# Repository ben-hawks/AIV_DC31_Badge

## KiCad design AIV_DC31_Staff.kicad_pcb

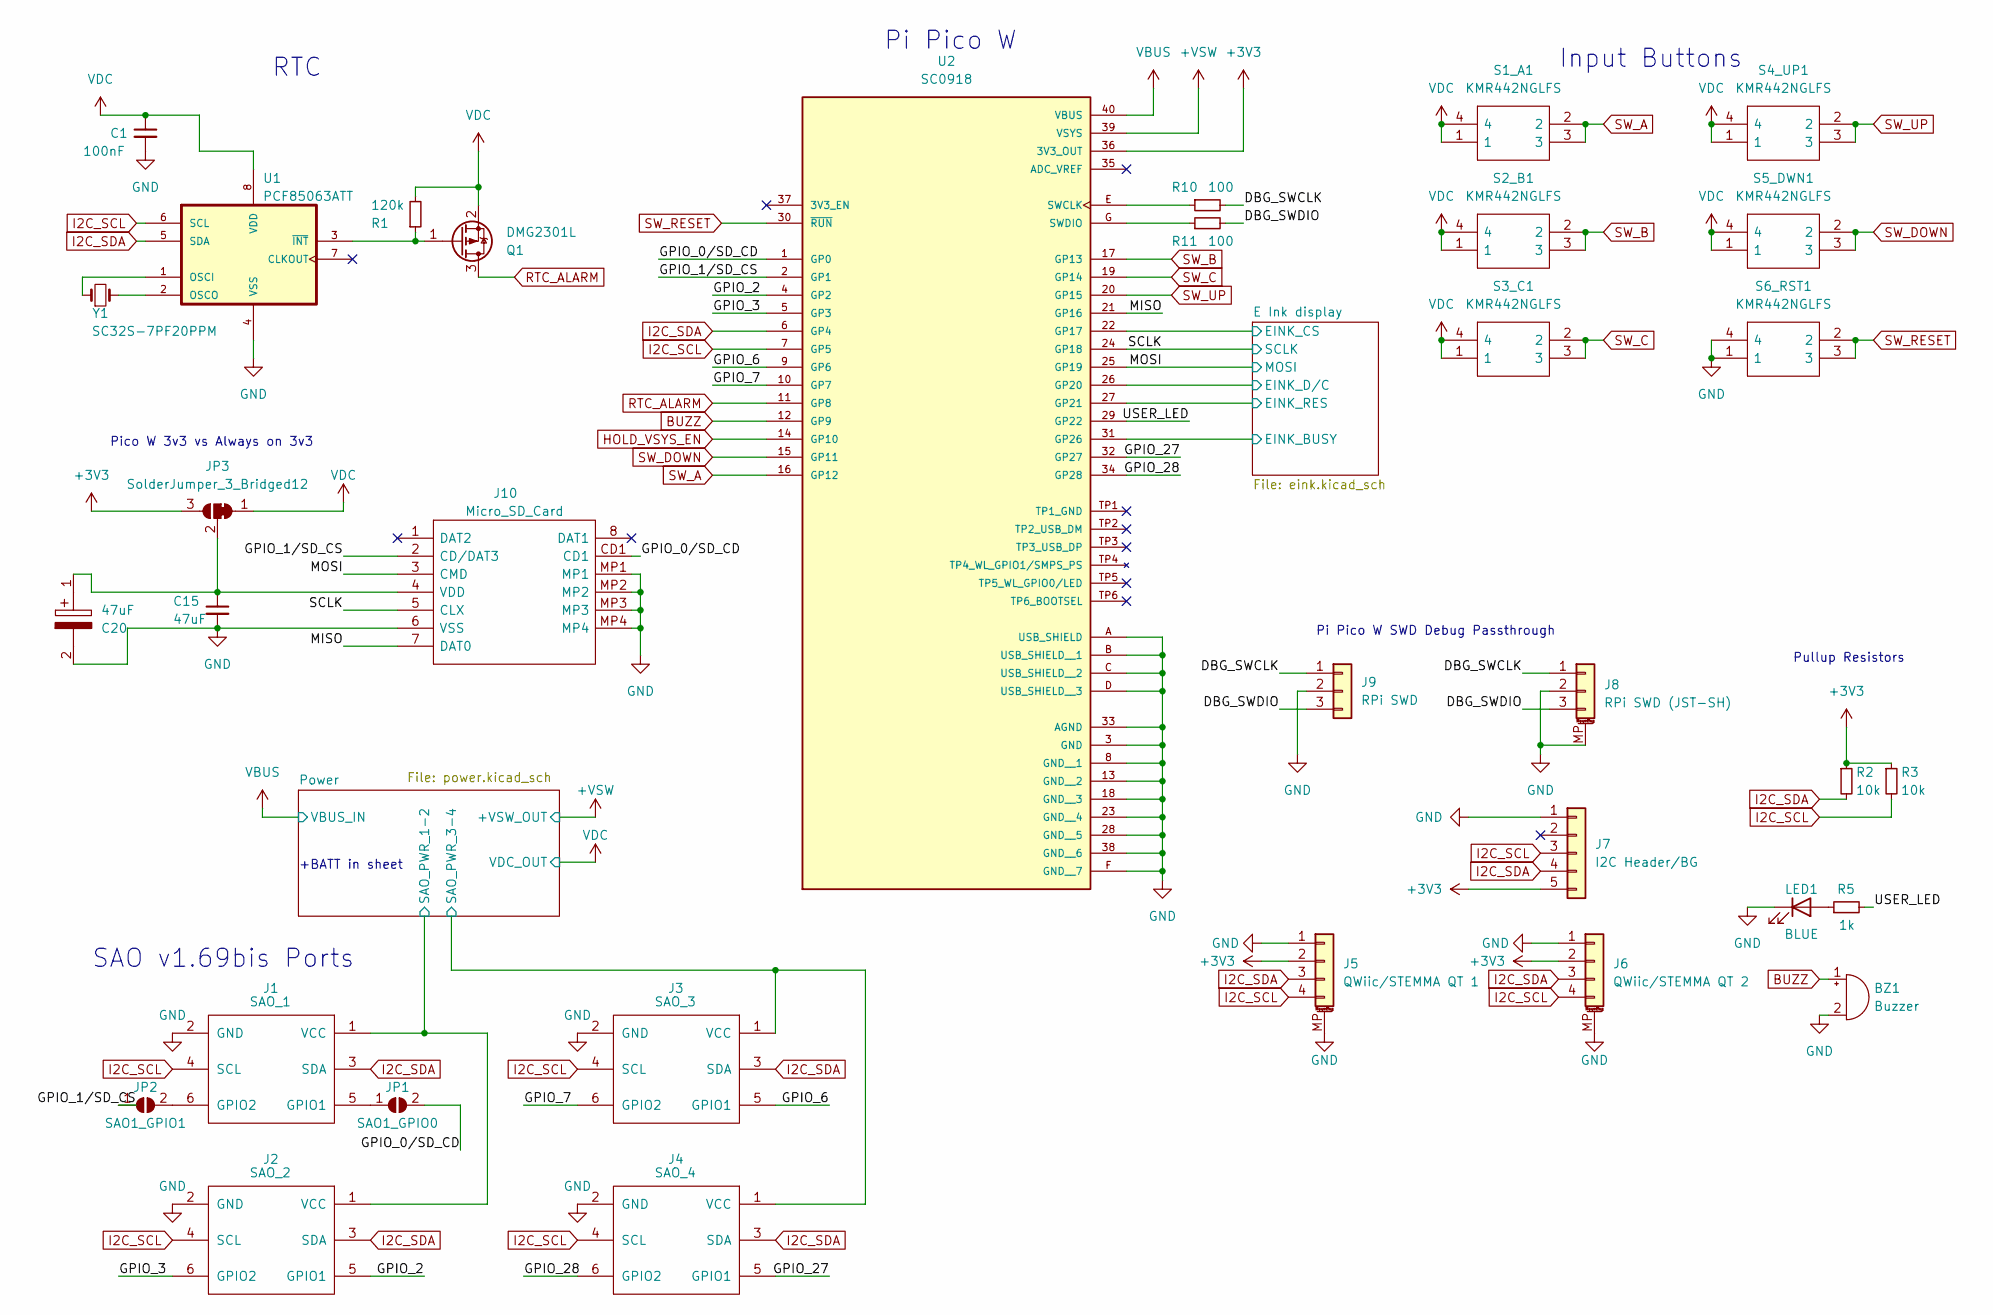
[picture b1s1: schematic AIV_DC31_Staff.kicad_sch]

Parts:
BZ1: Buzzer; Buzzer_CUI_CPT-9019S-SMT
C1: 100nF; C_0805_2012Metric_Pad1.18x1.45mm_HandSolder
C15: 47uF; C_0805_2012Metric_Pad1.18x1.45mm_HandSolder
C20: 47uF; CAPAE660X630N; Mouser Part Number 661-HHXC250A470MF61G
J1: SAO_1; Badgelife-SAOv169-BADGE-2x3
J2: SAO_2; Badgelife-SAOv169-BADGE-2x3
J3: SAO_3; Badgelife-SAOv169-BADGE-2x3
J4: SAO_4; Badgelife-SAOv169-BADGE-2x3
J5: QWiic/STEMMA QT 1; JST_SH_SM04B-SRSS-TB_1x04-1MP_P1.00mm_Horizontal; Part Number SM04B-SRSS-TB(LF)(SN)
J6: QWiic/STEMMA QT 2; JST_SH_SM04B-SRSS-TB_1x04-1MP_P1.00mm_Horizontal; Part Number SM04B-SRSS-TB(LF)(SN)
J7: I2C Header/BG; PinHeader_1x05_P2.00mm_Vertical
J8: RPi SWD (JST-SH); JST_SH_SM03B-SRSS-TB_1x03-1MP_P1.00mm_Horizontal
J9: RPi SWD; PinHeader_1x03_P2.00mm_Vertical
J10: Micro_SD_Card; TF101AP3; Manufacturer_Part_Number TF-101A-P3
JP1: SAO1_GPIO0; SolderJumper-2_P1.3mm_Open_RoundedPad1.0x1.5mm
JP2: SAO1_GPIO1; SolderJumper-2_P1.3mm_Open_RoundedPad1.0x1.5mm
JP3: SolderJumper_3_Bridged12; SolderJumper-3_P1.3mm_Bridged12_RoundedPad1.0x1.5mm
LED1: BLUE; LED_1206_3216Metric_Pad1.42x1.75mm_HandSolder
Q1: DMG2301L; SOT-23
R1: 120k; R_0805_2012Metric_Pad1.20x1.40mm_HandSolder
R2, R3: 10k; R_0805_2012Metric_Pad1.20x1.40mm_HandSolder
R5: 1k; R_0805_2012Metric_Pad1.20x1.40mm_HandSolder
R10, R11: 100; R_0805_2012Metric_Pad1.20x1.40mm_HandSolder
S1_A1, S2_B1, S3_C1, S4_UP1, S5_DWN1, S6_RST1: KMR442NGLFS; KMR442NGLFS_CNK; Mouser Part Number 611-KMR442NGLFS
U1: PCF85063ATT; SOP65P490X110-8N
U2: SC0918; MODULE_SC0918; PARTREV 2.1
Y1: SC32S-7PF20PPM; Crystal_SMD_3215-2Pin_3.2x1.5mm

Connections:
+3V3: J5.2, J6.2, J7.5, JP3.3 (B), R2.1, R3.1, U2.36 (3V3_OUT); also elsewhere on the board
+VSW: U2.39 (VSYS); also elsewhere on the board
/DBG_SWCLK: J8.1, J9.1, R10.2
/DBG_SWDIO: J8.3, J9.3, R11.2
/E Ink display/EINK_BUSY: U2.31 (GP26); also elsewhere on the board
/E Ink display/EINK_CS: U2.22 (GP17); also elsewhere on the board
/E Ink display/EINK_D/C: U2.26 (GP20); also elsewhere on the board
/E Ink display/EINK_RES: U2.27 (GP21); also elsewhere on the board
/GPIO_0/SD_CD: J10.CD1, JP1.2 (B), U2.1 (GP0)
/GPIO_1/SD_CS: J10.2 (CD/DAT3), JP2.1 (A), U2.2 (GP1)
/GPIO_2: J2.5 (GPIO1), U2.4 (GP2)
/GPIO_3: J2.6 (GPIO2), U2.5 (GP3)
/GPIO_6: J3.5 (GPIO1), U2.9 (GP6)
/GPIO_7: J3.6 (GPIO2), U2.10 (GP7)
/GPIO_27: J4.5 (GPIO1), U2.32 (GP27)
/GPIO_28: J4.6 (GPIO2), U2.34 (GP28)
/MISO: J10.7 (DAT0), U2.21 (GP16)
/MOSI: J10.3 (CMD), U2.25 (GP19); also elsewhere on the board
/Power/SAO_PWR_1-2: J1.1 (VCC), J2.1 (VCC); also elsewhere on the board
/Power/SAO_PWR_3-4: J3.1 (VCC), J4.1 (VCC); also elsewhere on the board
/SCLK: J10.5 (CLX), U2.24 (GP18); also elsewhere on the board
/USER_LED: R5.2, U2.29 (GP22)
BUZZ: BZ1.1 (-), U2.12 (GP9)
GND: BZ1.2 (+), C1.2, C15.2, C20.2, J1.2 (GND), J2.2 (GND), J3.2 (GND), J4.2 (GND), J5.1, J5.MP (MountPin), J6.1, J6.MP (MountPin), J7.1, J8.2, J8.MP (MountPin), J9.2, J10.6 (VSS), J10.MP1, J10.MP2, J10.MP3, J10.MP4, LED1.1 (K), S6_RST1.1, S6_RST1.4, U1.4 (VSS), U2.3 (GND), U2.8 (GND__1), U2.13 (GND__2), U2.18 (GND__3), U2.23 (GND__4), U2.28 (GND__5), U2.33 (AGND), U2.38 (GND__6), U2.A (USB_SHIELD), U2.B (USB_SHIELD__1), U2.C (USB_SHIELD__2), U2.D (USB_SHIELD__3), U2.F (GND__7); also elsewhere on the board
HOLD_VSYS_EN: U2.14 (GP10); also elsewhere on the board
I2C_SCL: J1.4 (SCL), J2.4 (SCL), J3.4 (SCL), J4.4 (SCL), J5.4, J6.4, J7.3, R3.2, U1.6 (SCL), U2.7 (GP5)
I2C_SDA: J1.3 (SDA), J2.3 (SDA), J3.3 (SDA), J4.3 (SDA), J5.3, J6.3, J7.4, R2.2, U1.5 (SDA), U2.6 (GP4)
unnamed: C15.1, C20.1, J10.4 (VDD), JP3.2 (C)
unnamed: J1.5 (GPIO1), JP1.1 (A)
unnamed: J1.6 (GPIO2), JP2.2 (B)
unnamed: LED1.2 (A), R5.1
unnamed: Q1.1 (G), R1.1, U1.3 (~INT)
unnamed: R10.1, U2.E (SWCLK)
unnamed: R11.1, U2.G (SWDIO)
unnamed: U1.1 (OSCI), Y1.1
unnamed: U1.2 (OSCO), Y1.2
RTC_ALARM: Q1.3 (D), U2.11 (GP8); also elsewhere on the board
SW_A: S1_A1.2, S1_A1.3, U2.16 (GP12); also elsewhere on the board
SW_B: S2_B1.2, S2_B1.3, U2.17 (GP13); also elsewhere on the board
SW_C: S3_C1.2, S3_C1.3, U2.19 (GP14); also elsewhere on the board
SW_DOWN: S5_DWN1.2, S5_DWN1.3, U2.15 (GP11); also elsewhere on the board
SW_RESET: S6_RST1.2, S6_RST1.3, U2.30 (~RUN)
SW_UP: S4_UP1.2, S4_UP1.3, U2.20 (GP15); also elsewhere on the board
VBUS: U2.40 (VBUS); also elsewhere on the board
VDC: C1.1, JP3.1 (A), Q1.2 (S), R1.2, S1_A1.1, S1_A1.4, S2_B1.1, S2_B1.4, S3_C1.1, S3_C1.4, S4_UP1.1, S4_UP1.4, S5_DWN1.1, S5_DWN1.4, U1.8 (VDD); also elsewhere on the board

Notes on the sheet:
RTC
SAO v1.69bis Ports
Pullup Resistors
+BATT in sheet
Input Buttons
Pico W 3v3 vs Always on 3v3
Pi Pico W
Pi Pico W SWD Debug Passthrough

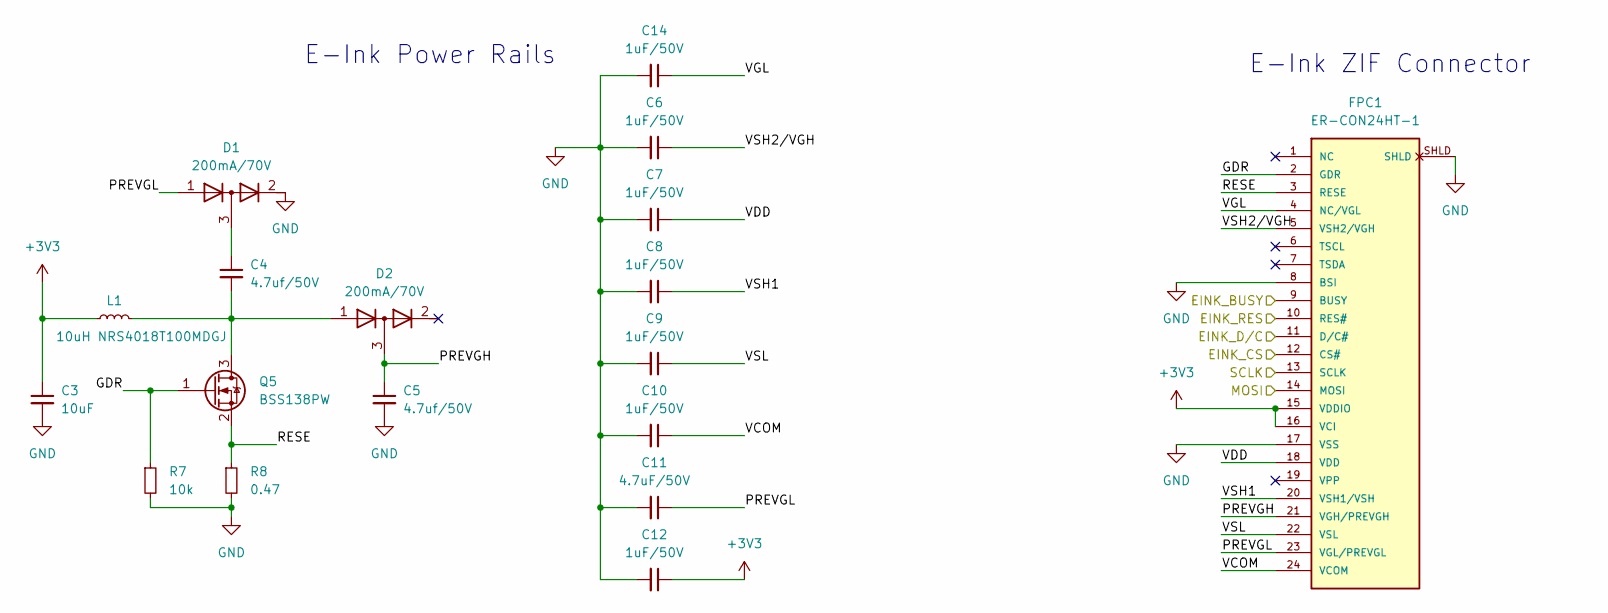
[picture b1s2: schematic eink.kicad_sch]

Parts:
C3: 10uF; C_0805_2012Metric_Pad1.18x1.45mm_HandSolder
C4, C5: 4.7uf/50V; C_0805_2012Metric_Pad1.18x1.45mm_HandSolder
C6, C7, C8, C9, C10, C12, C14: 1uF/50V; C_0805_2012Metric_Pad1.18x1.45mm_HandSolder
C11: 4.7uF/50V; C_0805_2012Metric_Pad1.18x1.45mm_HandSolder
D1, D2: 200mA/70V; SOT-23
FPC1: ER-CON24HT-1; ER-CON24HT-1-REV
L1: 10uH NRS4018T100MDGJ; L_Taiyo-Yuden_NR-40xx_HandSoldering
Q5: BSS138PW; SOT-323_SC-70
R7: 10k; R_0805_2012Metric_Pad1.20x1.40mm_HandSolder
R8: 0.47; R_0603_1608Metric_Pad0.98x0.95mm_HandSolder

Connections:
+3V3: C3.1, C12.1, FPC1.15 (VDDIO), FPC1.16 (VCI), L1.1; also elsewhere on the board
/E Ink display/EINK_BUSY: FPC1.9 (BUSY); also elsewhere on the board
/E Ink display/EINK_CS: FPC1.12 (CS#); also elsewhere on the board
/E Ink display/EINK_D/C: FPC1.11 (D/C#); also elsewhere on the board
/E Ink display/EINK_RES: FPC1.10 (RES#); also elsewhere on the board
/E Ink display/GDR: FPC1.2 (GDR), Q5.1 (G), R7.1
/E Ink display/PREVGH: C5.1, D2.3 (common), FPC1.21 (VGH/PREVGH)
/E Ink display/PREVGL: C11.1, D1.1 (A), FPC1.23 (VGL/PREVGL)
/E Ink display/RESE: FPC1.3 (RESE), Q5.2 (S), R8.1
/E Ink display/VCOM: C10.1, FPC1.24 (VCOM)
/E Ink display/VDD: C7.1, FPC1.18 (VDD)
/E Ink display/VGL: C14.1, FPC1.4 (NC/VGL)
/E Ink display/VSH1: C8.1, FPC1.20 (VSH1/VSH)
/E Ink display/VSH2/VGH: C6.1, FPC1.5 (VSH2/VGH)
/E Ink display/VSL: C9.1, FPC1.22 (VSL)
/MOSI: FPC1.14 (MOSI); also elsewhere on the board
/SCLK: FPC1.13 (SCLK); also elsewhere on the board
GND: C3.2, C5.2, C6.2, C7.2, C8.2, C9.2, C10.2, C11.2, C12.2, C14.2, D1.2 (K), FPC1.8 (BSI), FPC1.17 (VSS), FPC1.SHLD, R7.2, R8.2; also elsewhere on the board
unnamed: C4.1, D1.3 (common)
unnamed: C4.2, D2.1 (A), L1.2, Q5.3 (D)

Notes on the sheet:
E-Ink Power Rails
E-Ink ZIF Connector

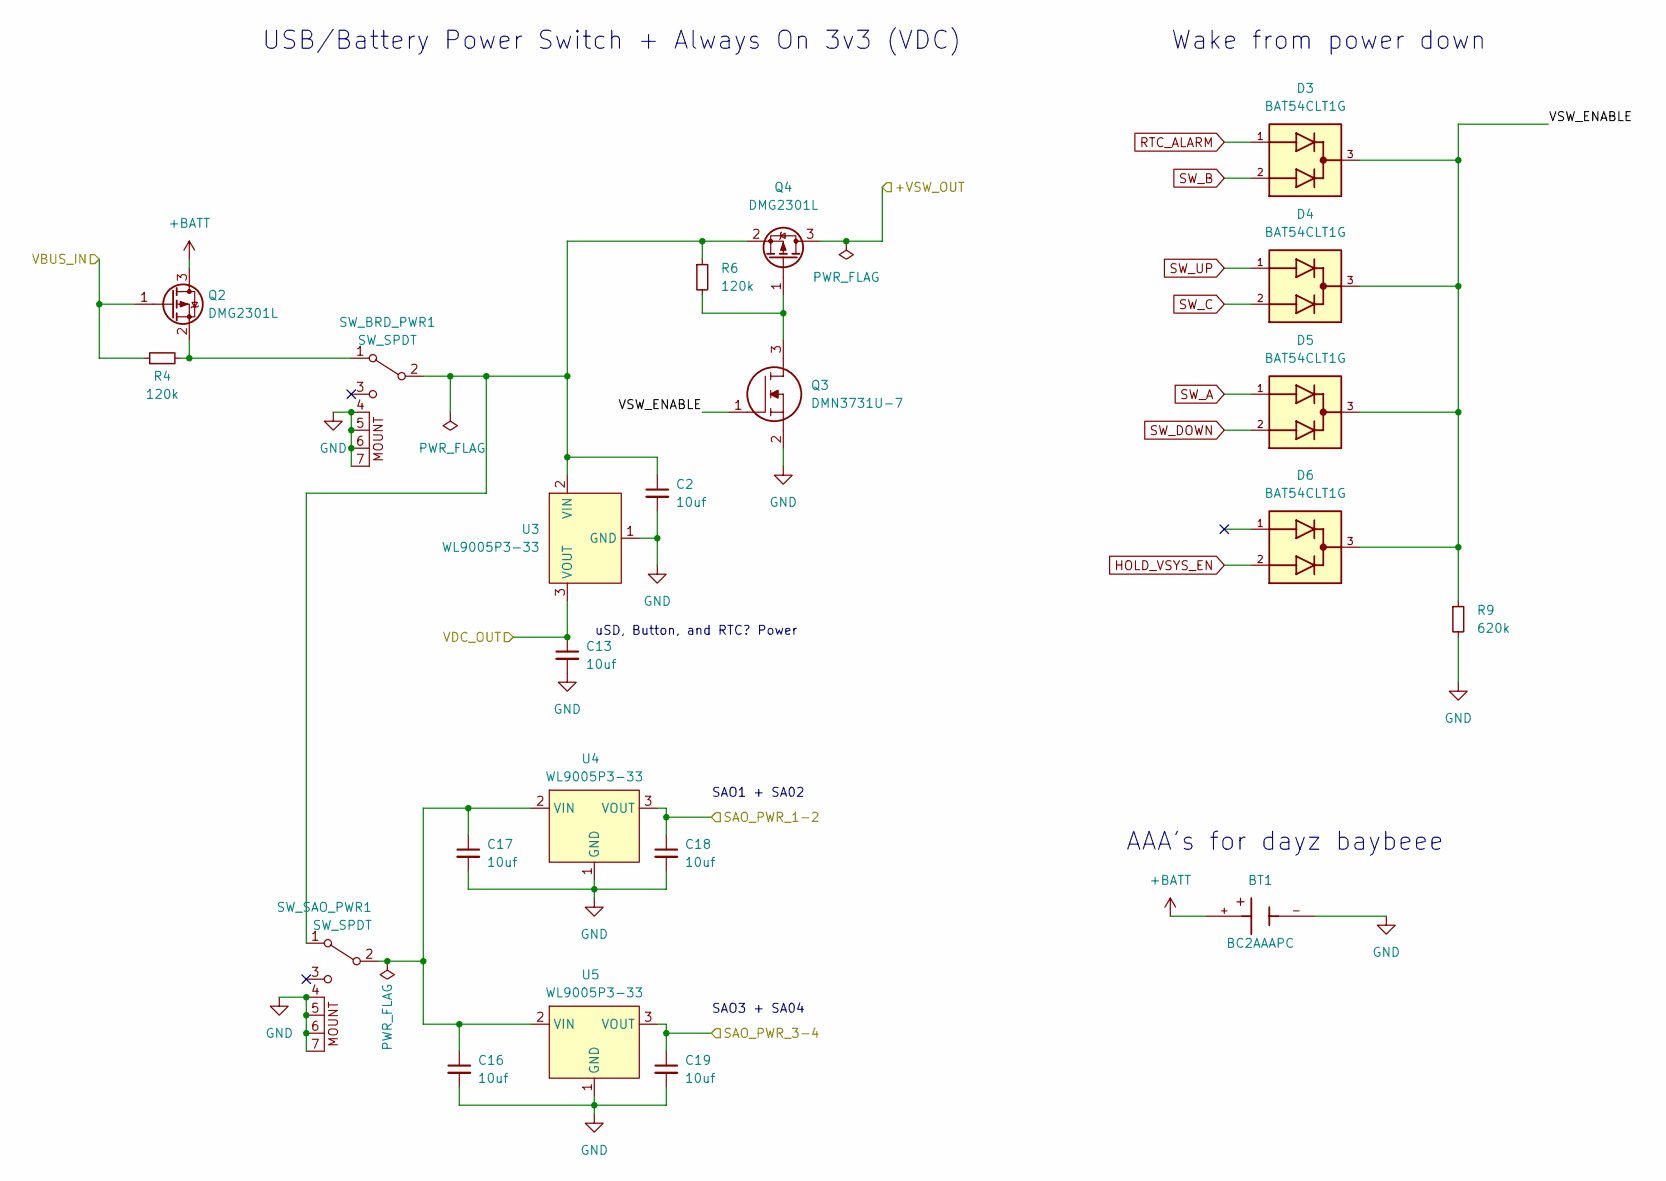
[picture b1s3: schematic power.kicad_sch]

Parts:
BT1: BC2AAAPC; BAT_BC2AAAPC; PARTREV L
C2, C13, C16, C17, C18, C19: 10uf; C_0805_2012Metric_Pad1.18x1.45mm_HandSolder
D3, D4, D5, D6: BAT54CLT1G; SOT95P237X111-3N; PARTREV 12
Q2, Q4: DMG2301L; SOT-23
Q3: DMN3731U-7; SOT-23; Manufacturer_Part_Number DMN3731U-7; Mouser Part Number 621-DMN3731U-7
R4, R6: 120k; R_0805_2012Metric_Pad1.20x1.40mm_HandSolder
R9: 620k; R_0805_2012Metric_Pad1.20x1.40mm_HandSolder
SW_BRD_PWR1: SW_SPDT; SW-SMD_G-SWITCH_MK-12C02-G015
SW_SAO_PWR1: SW_SPDT; SW-SMD_G-SWITCH_MK-12C02-G015
U3, U4, U5: WL9005P3-33; SOT-89-3

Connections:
+BATT: BT1.+, Q2.3 (D)
+VSW: Q4.3 (D); also elsewhere on the board
/Power/SAO_PWR_1-2: C18.1, U4.3 (VOUT); also elsewhere on the board
/Power/SAO_PWR_3-4: C19.1, U5.3 (VOUT); also elsewhere on the board
/Power/VSW_ENABLE: D3.3, D4.3, D5.3, D6.3, Q3.1, R9.1
GND: BT1.-, C2.2, C13.2, C16.2, C17.2, C18.2, C19.2, Q3.2, R9.2, SW_BRD_PWR1.4 (GND), SW_BRD_PWR1.5 (GND), SW_BRD_PWR1.6 (GND), SW_BRD_PWR1.7 (GND), SW_SAO_PWR1.4 (GND), SW_SAO_PWR1.5 (GND), SW_SAO_PWR1.6 (GND), SW_SAO_PWR1.7 (GND), U3.1 (GND), U4.1 (GND), U5.1 (GND); also elsewhere on the board
HOLD_VSYS_EN: D6.2; also elsewhere on the board
unnamed: C2.1, Q4.2 (S), R6.1, SW_BRD_PWR1.2 (B), SW_SAO_PWR1.1 (A), U3.2 (VIN)
unnamed: C16.1, C17.1, SW_SAO_PWR1.2 (B), U4.2 (VIN), U5.2 (VIN)
unnamed: Q2.2 (S), R4.2, SW_BRD_PWR1.1 (A)
unnamed: Q3.3, Q4.1 (G), R6.2
RTC_ALARM: D3.1; also elsewhere on the board
SW_A: D5.1; also elsewhere on the board
SW_B: D3.2; also elsewhere on the board
SW_C: D4.2; also elsewhere on the board
SW_DOWN: D5.2; also elsewhere on the board
SW_UP: D4.1; also elsewhere on the board
VBUS: Q2.1 (G), R4.1; also elsewhere on the board
VDC: C13.1, U3.3 (VOUT); also elsewhere on the board

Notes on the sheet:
Wake from power down
SAO1 + SA02
uSD, Button, and RTC? Power
USB/Battery Power Switch + Always On 3v3 (VDC)
AAA's for dayz baybeee
SAO3 + SA04

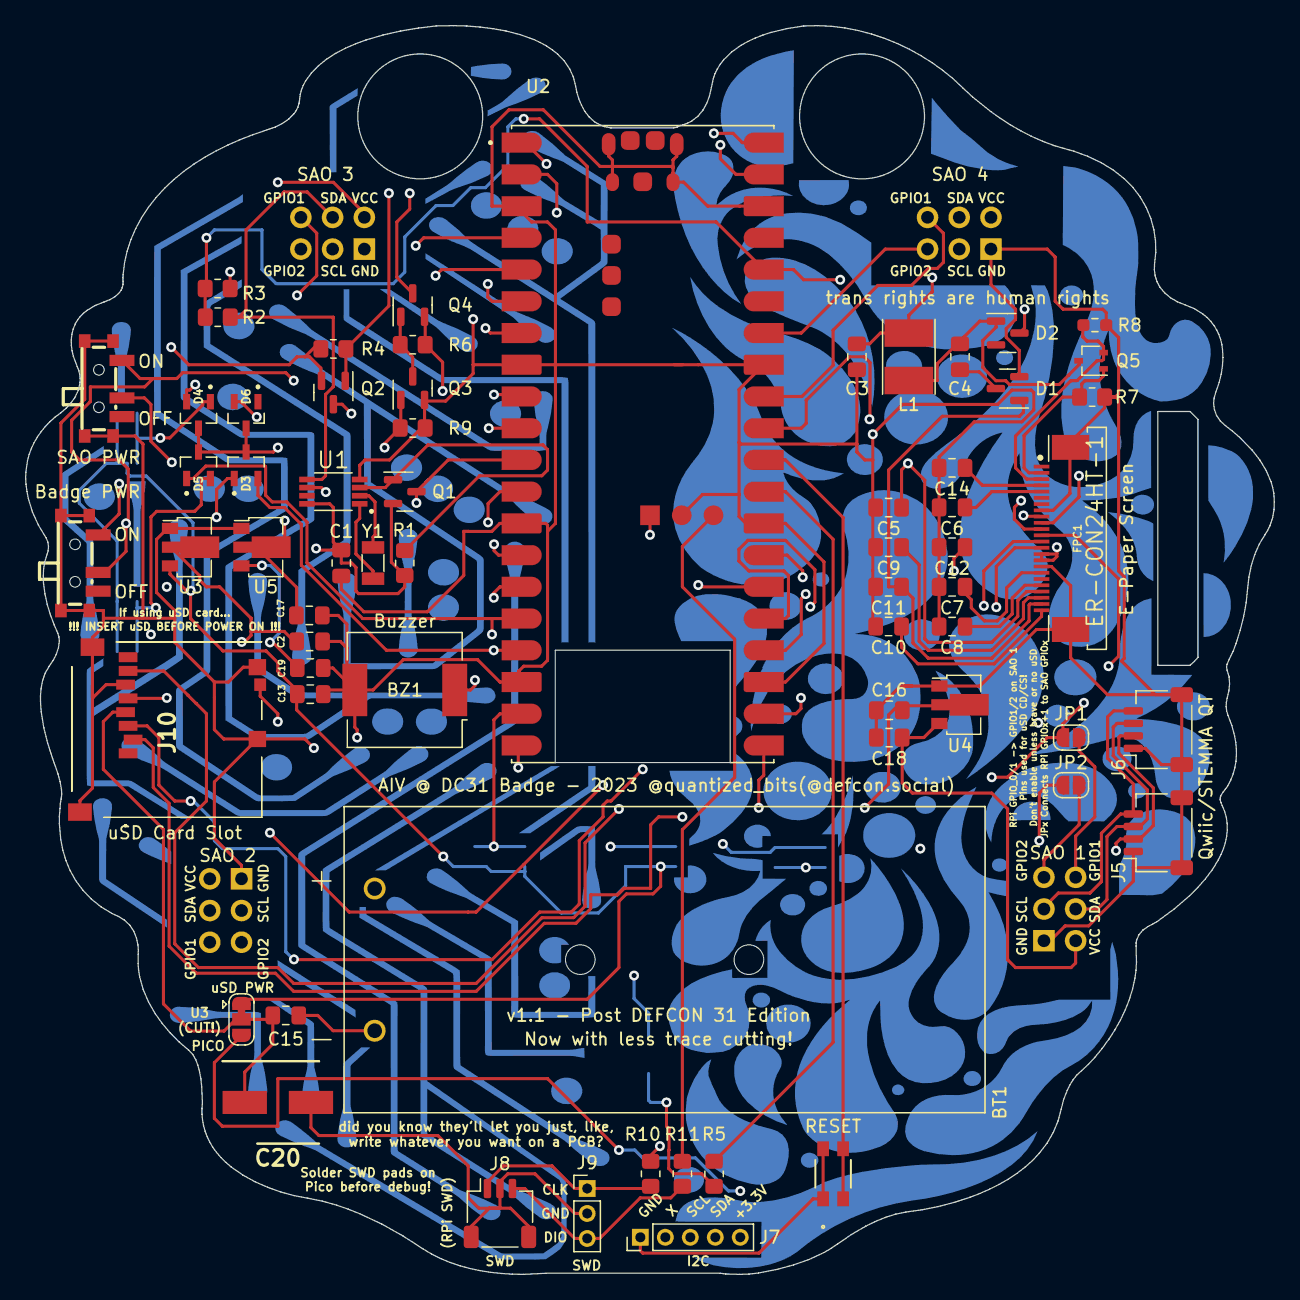
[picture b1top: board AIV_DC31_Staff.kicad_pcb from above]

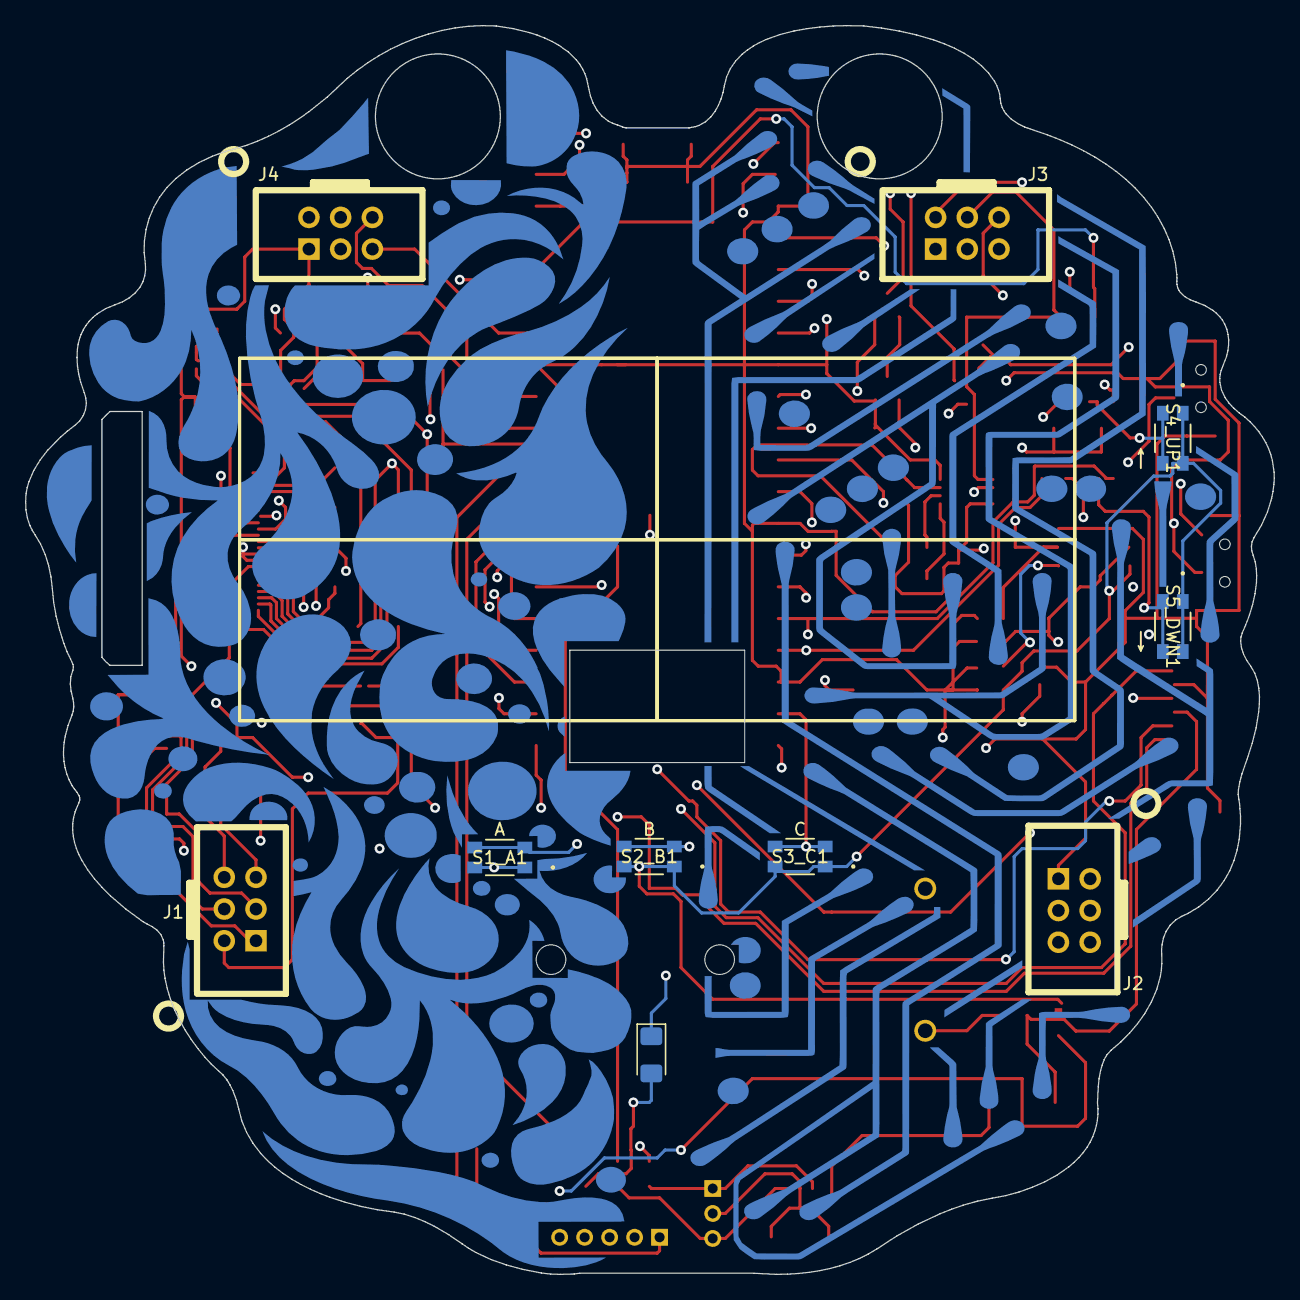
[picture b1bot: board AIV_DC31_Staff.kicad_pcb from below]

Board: 4 copper layers, 100.0 x 100.0 mm, 74 parts (10 on the bottom side), 63 nets.

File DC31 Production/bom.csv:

Designator,Footprint,Quantity,Value,LCSC Part #
BT1,BAT_BC2AAAPC,1,BC2AAAPC,
BZ1,Buzzer_CUI_CPT-9019S-SMT,1,Buzzer,C968734
C1,805,1,100nF,
C10,805,1,1uF/50V,
C11,805,1,4.7uF/50V,
C12,805,1,1uF/50V,
C13,805,1,10uf,
C14,805,1,1uF/50V,
C15,805,1,47uF,
C16,805,1,10uf,
C17,805,1,10uf,
C18,805,1,10uf,
C19,805,1,10uf,
C2,805,1,10uf,
C20,CAPAE660X630N,1,47uF,C2161680
C3,805,1,10uF,
C4,805,1,4.7uf/50V,
C5,805,1,4.7uf/50V,
C6,805,1,1uF/50V,
C7,805,1,1uF/50V,
C8,805,1,1uF/50V,
C9,805,1,1uF/50V,
"D1, D2",SOT-23,2,200mA/70V,
"D3, D4, D5, D6",SOT95P237X111-3N,4,BAT54CLT1G,
FPC1,ER-CON24HT-1-REV,1,ER-CON24HT-1,C11092
J1,Badgelife-SAOv169-BADGE-2x3,1,SAO_1,
J10,TF101AP3,1,Micro_SD_Card,C266607
J2,Badgelife-SAOv169-BADGE-2x3,1,SAO_2,
J3,Badgelife-SAOv169-BADGE-2x3,1,SAO_3,
J4,Badgelife-SAOv169-BADGE-2x3,1,SAO_4,
J5,JST_SH_SM04B-SRSS-TB_1x04-1MP_P1.00mm_Horizontal,1,QWiic/STEMMA QT 1,C160404
J6,JST_SH_SM04B-SRSS-TB_1x04-1MP_P1.00mm_Horizontal,1,QWiic/STEMMA QT 2,C160404
J7,PinHeader_1x05_P2.00mm_Vertical,1,I2C Header/BG,
J8,JST_SH_SM03B-SRSS-TB_1x03-1MP_P1.00mm_Horizontal,1,RPi SWD (JST-SH),C160403
J9,PinHeader_1x03_P2.00mm_Vertical,1,RPi SWD,
JP1,SolderJumper-2_P1.3mm_Open_RoundedPad1.0x1.5mm,1,SAO1_GPIO0,
JP2,SolderJumper-2_P1.3mm_Open_RoundedPad1.0x1.5mm,1,SAO1_GPIO1,
JP3,SolderJumper-3_P1.3mm_Bridged12_RoundedPad1.0x1.5mm,1,SolderJumper_3_Bridged12,
L1,L_Taiyo-Yuden_NR-40xx_HandSoldering,1,10uH NRS4018T100MDGJ,C222882
LED1,1206,1,BLUE,
"Q1, Q2, Q4",SOT-23,3,DMG2301L,
Q3,SOT-23,1,DMN3731U-7,C459540
Q5,SOT-323_SC-70,1,BSS138PW,
R1,805,1,120k,
R10,805,1,100,
R11,805,1,100,
R2,805,1,10k,
R3,805,1,10k,
R4,805,1,120k,
R5,805,1,1k,
R6,805,1,120k,
R7,805,1,10k,
R8,603,1,0.47,C175657
R9,805,1,620k,
"S1_A1, S2_B1, S3_C1, S4_UP1, S5_DWN1, S6_RST1",KMR442NGLFS_CNK,6,KMR442NGLFS,C221692
"SW_BRD_PWR1, SW_SAO_PWR1",SW-SMD_G-SWITCH_MK-12C02-G015,2,SW_SPDT,C2911519
U1,SOP65P490X110-8N,1,PCF85063ATT,C165608
U2,MODULE_SC0918,1,SC0918,
"U3, U4, U5",SOT-89-3,3,WL9005P3-33,C2688248
Y1,Crystal_SMD_3215-2Pin_3.2x1.5mm,1,SC32S-7PF20PPM ,C2650468

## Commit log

2024-05-24 Initial Commit of AIV DC31 Badge Files
2024-05-24 Add in missing BOM Files
